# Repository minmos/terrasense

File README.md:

### Quick Overview
* **`firmware`**: contains the esp-idf firmware running on the esp32c6
* **`cad`**: contains the CAD files for the case housing the sockets, the 12V PSU, the relais/hv pcb, and an extension for that box housing the main pcb
* **`pcb`**: contains the KiCad files for the relais/hv pcb as well as the main pcb

### DEMO
Here is a quick demo video of our Terrasense implementation in action:

https://github.com/user-attachments/assets/7964f494-83c7-4bb1-9dd9-c3dd94d3becd

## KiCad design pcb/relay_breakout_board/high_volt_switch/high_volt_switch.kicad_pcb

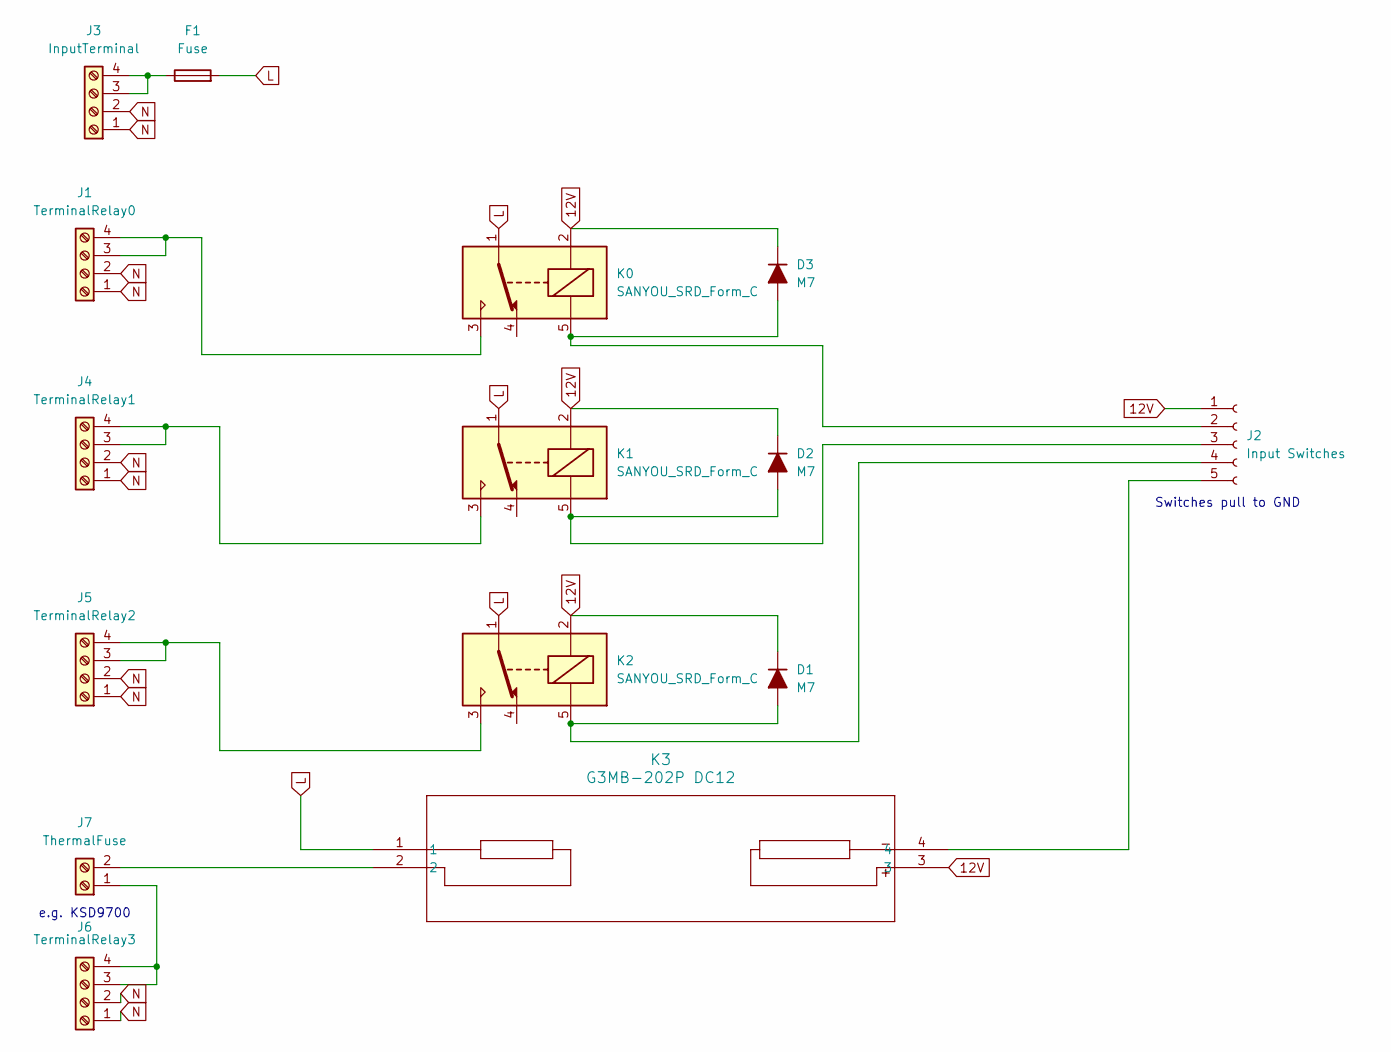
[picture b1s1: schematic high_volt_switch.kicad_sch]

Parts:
D1, D2, D3: M7; D_SMA
F1: Fuse; Fuseholder_Cylinder-5x20mm_Schurter_0031_8201_Horizontal_Op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
J1: TerminalRelay0; Altech_AK100_1x04_P5.00mm
J2: Input Switches; JST_XH_B5B-XH-A_1x05_P2.50mm_Vertical
J3: InputTerminal; Altech_AK100_1x04_P5.00mm
J4: TerminalRelay1; Altech_AK100_1x04_P5.00mm
J5: TerminalRelay2; Altech_AK100_1x04_P5.00mm
J6: TerminalRelay3; Altech_AK100_1x04_P5.00mm
J7: ThermalFuse; Altech_AK100_1x02_P5.00mm
K0, K1, K2: SANYOU_SRD_Form_C; Relay_SPDT_SANYOU_SRD_Series_Form_C
K3: G3MB-202P DC12; G3MB-202P DC5_OMR

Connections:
12V: D1.1 (K), D2.1 (K), D3.1 (K), J2.1, K0.2, K1.2, K2.2, K3.3
L: F1.2, K0.1, K1.1, K2.1, K3.1
N: J1.1, J1.2, J3.1, J3.2, J4.1, J4.2, J5.1, J5.2, J6.1, J6.2
unnamed: D1.2 (A), J2.4, K2.5
unnamed: D2.2 (A), J2.3, K1.5
unnamed: D3.2 (A), J2.2, K0.5
unnamed: J1.3, J1.4, K0.3
unnamed: J2.5, K3.4
unnamed: F1.1, J3.3, J3.4
unnamed: J4.3, J4.4, K1.3
unnamed: J5.3, J5.4, K2.3
unnamed: J6.3, J6.4, J7.1
unnamed: J7.2, K3.2

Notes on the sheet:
Switches pull to GND
e.g. KSD9700

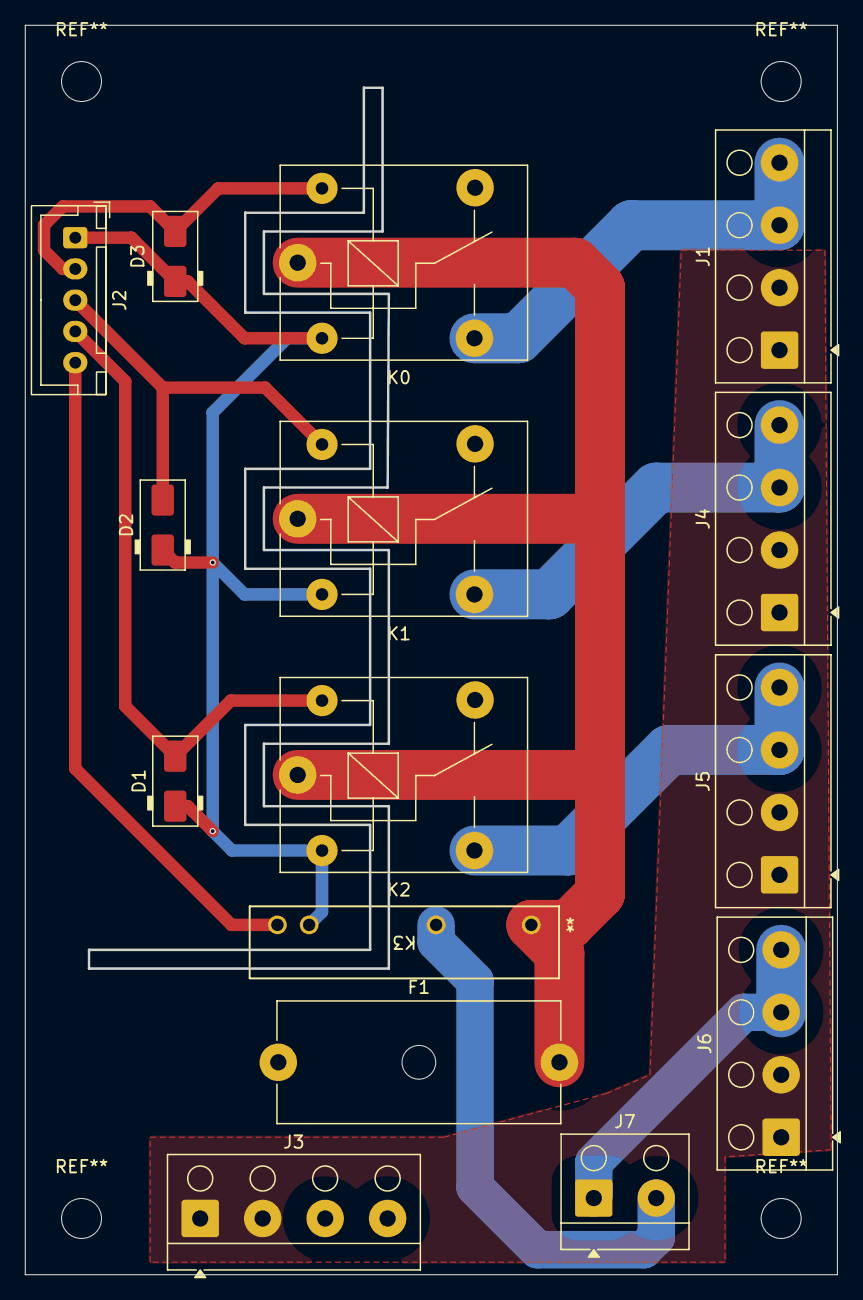
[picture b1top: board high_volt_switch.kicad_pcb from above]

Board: 2 copper layers, 64.9 x 99.9 mm, 15 parts (0 on the bottom side), 13 nets.

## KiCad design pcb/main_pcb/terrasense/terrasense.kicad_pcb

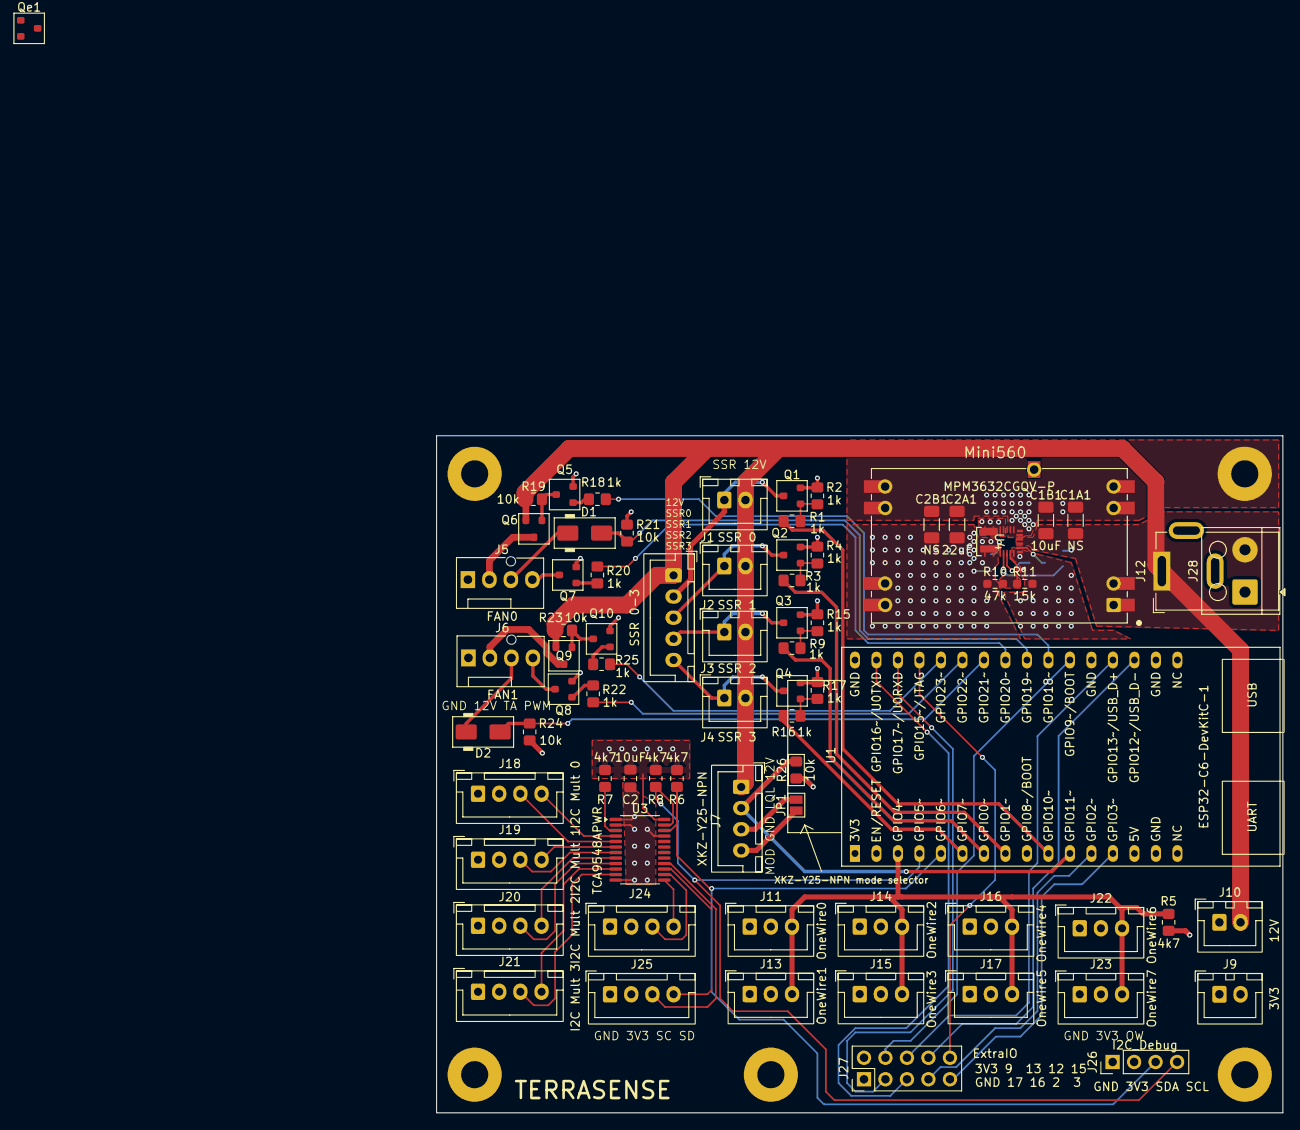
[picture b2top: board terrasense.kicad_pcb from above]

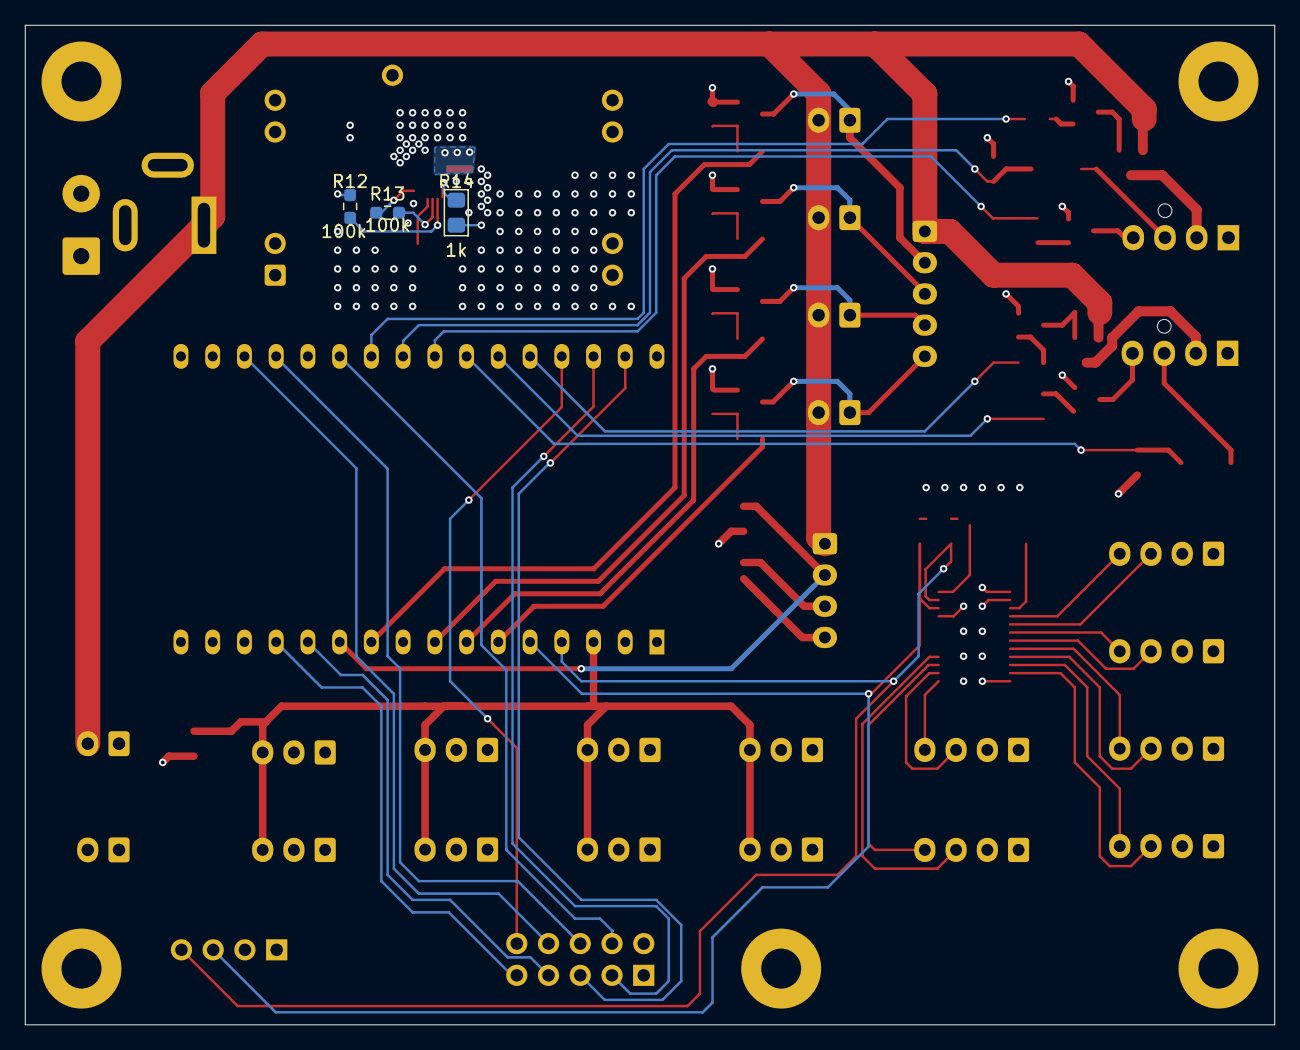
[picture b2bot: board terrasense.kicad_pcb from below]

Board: 4 copper layers, 100.0 x 80.0 mm, 77 parts (3 on the bottom side), 65 nets.

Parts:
C1A1, C2B1: NS; C_1206_3216Metric_Pad1.33x1.80mm_HandSolder
C1B1: 10uF; C_1206_3216Metric_Pad1.33x1.80mm_HandSolder
C2: 10uF; C_0805_2012Metric_Pad1.18x1.45mm_HandSolder
C2A1: 22uF; C_1206_3216Metric_Pad1.33x1.80mm_HandSolder
D1, D2: M7; D_SMA
J1: SSR 0; JST_XH_B2B-XH-A_1x02_P2.50mm_Vertical
J2: SSR 1; JST_XH_B2B-XH-A_1x02_P2.50mm_Vertical
J3: SSR 2; JST_XH_B2B-XH-A_1x02_P2.50mm_Vertical
J4: SSR 3; JST_XH_B2B-XH-A_1x02_P2.50mm_Vertical
J5: FAN0; FanPinHeader_1x04_P2.54mm_Vertical
J6: FAN1; FanPinHeader_1x04_P2.54mm_Vertical
J7: XKZ-Y25-NPN; JST_XH_B4B-XH-A_1x04_P2.50mm_Vertical
J8: SSR 0-3; JST_XH_B5B-XH-A_1x05_P2.50mm_Vertical
J9: 3V3; JST_XH_B2B-XH-A_1x02_P2.50mm_Vertical
J10: 12V; JST_XH_B2B-XH-A_1x02_P2.50mm_Vertical
J11: OneWire0; JST_XH_B3B-XH-A_1x03_P2.50mm_Vertical
J12: 12V In; BarrelJack_GCT_DCJ200-10-A_Horizontal
J13: OneWire1; JST_XH_B3B-XH-A_1x03_P2.50mm_Vertical
J14: OneWire2; JST_XH_B3B-XH-A_1x03_P2.50mm_Vertical
J15: OneWire3; JST_XH_B3B-XH-A_1x03_P2.50mm_Vertical
J16: OneWire4; JST_XH_B3B-XH-A_1x03_P2.50mm_Vertical
J17: OneWire5; JST_XH_B3B-XH-A_1x03_P2.50mm_Vertical
J18: I2C Mult 0; JST_XH_B4B-XH-A_1x04_P2.50mm_Vertical
J19: I2C Mult 1; JST_XH_B4B-XH-A_1x04_P2.50mm_Vertical
J20: I2C Mult 2; JST_XH_B4B-XH-A_1x04_P2.50mm_Vertical
J21: I2C Mult 3; JST_XH_B4B-XH-A_1x04_P2.50mm_Vertical
J22: OneWire6; JST_XH_B3B-XH-A_1x03_P2.50mm_Vertical
J23: OneWire7; JST_XH_B3B-XH-A_1x03_P2.50mm_Vertical
J24: I2C Mult 4; JST_XH_B4B-XH-A_1x04_P2.50mm_Vertical
J25: I2C Mult 5; JST_XH_B4B-XH-A_1x04_P2.50mm_Vertical
J26: I2C_Debug; PinHeader_1x04_P2.54mm_Vertical
J27: ExtraIO; PinHeader_2x05_P2.54mm_Vertical
J28: 12V_In; Altech_AK100_1x02_P5.00mm
JP1: XKZ-Y25-NPN mode selector; SolderJumper-2_P1.3mm_Open_Pad1.0x1.5mm
Q1, Q2, Q3, Q4, Q5, Q7, Q8, Q10: MMBT2222A; SOT-23
Q6, Q9: A3401; SOT-23
Qe1: A3401; SOT-23
R1, R2, R3, R4, R9, R14, R15, R16, R17, R18, R20, R22, R25: 1k; R_0805_2012Metric_Pad1.20x1.40mm_HandSolder
R5, R6, R7, R8: 4k7; R_0805_2012Metric_Pad1.20x1.40mm_HandSolder
R10: 47k; R_0603_1608Metric_Pad0.98x0.95mm_HandSolder
R11: 15k; R_0603_1608Metric_Pad0.98x0.95mm_HandSolder
R12, R13: 100k; R_0603_1608Metric_Pad0.98x0.95mm_HandSolder
R19, R21, R23, R24, R26: 10k; R_0805_2012Metric_Pad1.20x1.40mm_HandSolder
U1: ESP32-C6-DevKitC-1
U2: Mini560
U3: TCA9548APWR; TSSOP-24_4.4x7.8mm_P0.65mm
U4: MPM3632CGQV-P; QFN3p0x5p0x1p6_MPM3632C_MNP

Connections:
3V3: C2.1, C2A1.1, C2B1.1, J9.2, J11.2, J13.2, J14.2, J15.2, J16.2, J17.2, J18.2, J19.2, J20.2, J21.2, J22.2, J23.2, J24.2, J25.2, J26.2, J27.2, R5.2, R6.1, R7.1, R8.1, R10.1, R14.2, R21.1, R24.1, R26.1, U1.1 (3V3), U2.8 (VOUT+), U2.9 (VOUT+), U3.24 (VCC), U4.8 (OUT), U4.9 (OUT)
12V: C1A1.1, C1B1.1, J1.2, J2.2, J3.2, J4.2, J7.1, J8.1, J10.2, J12.1, J28.2, Q6.2 (S), Q9.2 (S), Qe1.2 (S), R12.1, R19.2, R23.2, U2.1 (VIN+), U2.2 (VIN+), U4.17 (VIN), U4.18 (VIN)
/FAN/FAN_0_12V_PWM: R18.2, U1.23 (GPIO18)
/FAN/FAN_0_PWM: R20.1, U1.25 (GPIO20)
/FAN/FAN_0_TACHO: D1.2 (A), R21.2, U1.24 (GPIO19)
/FAN/FAN_1_12V_PWM: R25.2, U1.28 (GPIO23)
/FAN/FAN_1_PWM: R22.1, U1.27 (GPIO22)
/FAN/FAN_1_TACHO: D2.2 (A), R24.2, U1.26 (GPIO21)
/GPIO2: J27.7, U1.12 (GPIO2)
/GPIO3: J27.9, U1.13 (GPIO3)
/GPIO9/BOOT: J27.4, U1.22 (GPIO9/BOOT)
/GPIO12/USB_D-: J27.8, U1.19 (GPIO12/USB_D-)
/GPIO13/USB_D+: J27.6, U1.20 (GPIO13/USB_D+)
/GPIO15/JTAG: J27.10, U1.29 (GPIO15/JTAG)
/GPIO16/U0TXD: J27.5, U1.31 (GPIO16/U0TXD)
/GPIO17/U0RXD: J27.3, U1.30 (GPIO17/U0RXD)
/I2C_MULT/I2C_SCL: J26.3, R6.2, U1.5 (GPIO6), U3.22 (SCL)
/I2C_MULT/I2C_SDA: J26.4, R8.2, U1.4 (GPIO5/MTDI), U3.23 (SDA)
/I2C_MULT/SC0: J18.3, U3.5 (SC0)
/I2C_MULT/SC1: J19.3, U3.7 (SC1)
/I2C_MULT/SC2: J20.3, U3.9 (SC2)
/I2C_MULT/SC3: J21.3, U3.11 (SC3)
/I2C_MULT/SC4: J24.3, U3.14 (SC4)
/I2C_MULT/SC5: J25.3, U3.16 (SC5)
/I2C_MULT/SD0: J18.4, U3.4 (SD0)
/I2C_MULT/SD1: J19.4, U3.6 (SD1)
/I2C_MULT/SD2: J20.4, U3.8 (SD2)
/I2C_MULT/SD3: J21.4, U3.10 (SD3)
/I2C_MULT/SD4: J24.4, U3.13 (SD4)
/I2C_MULT/SD5: J25.4, U3.15 (SD5)
/LIQUID_LEVEL/LIQUID_LEVEL: J7.2, R26.2, U1.11 (GPIO11)
/ONE_WIRE/OneWire: J11.3, J13.3, J14.3, J15.3, J16.3, J17.3, J22.3, J23.3, R5.1, U1.3 (GPIO4/MTMS)
/SSR/SSR_0_CTRL: R1.1, U1.10 (GPIO10)
/SSR/SSR_1_CTRL: R3.1, U1.8 (GPIO1)
/SSR/SSR_2_CTRL: R9.1, U1.7 (GPIO0)
/SSR/SSR_3_CTRL: R16.1, U1.6 (GPIO7)
/STEP_DOWN/EN: R12.2, U4.11 (EN)
/STEP_DOWN/VCC: R13.1, U4.16 (VCC)
GND: C1A1.2, C1B1.2, C2.2, C2A1.2, C2B1.2, J5.1, J6.1, J7.3, J9.1, J10.1, J11.1, J12.2, J13.1, J14.1, J15.1, J16.1, J17.1, J18.1, J19.1, J20.1, J21.1, J22.1, J23.1, J24.1, J25.1, J26.1, J27.1, J28.1, JP1.2 (B), Q1.2 (E), Q2.2 (E), Q3.2 (E), Q4.2 (E), Q5.2 (E), Q7.2 (E), Q8.2 (E), Q10.2 (E), R2.1, R4.1, R11.2, R15.1, R17.1, U1.15 (GND), U1.18 (GND), U1.21 (GND), U1.32 (GND), U2.3 (GND), U2.4 (GND), U2.6 (GND), U2.7 (GND), U3.1 (A0), U3.2 (A1), U3.12 (GND), U3.21 (A2), U4.1 (PGND), U4.2 (PGND), U4.14 (AGND), U4.15 (AGND), U4.19 (PGND), U4.20 (PGND)
unnamed: D1.1 (K), J5.3
unnamed: D2.1 (K), J6.3
unnamed: J1.1, J8.2, Q1.3 (C)
unnamed: J2.1, J8.3, Q2.3 (C)
unnamed: J3.1, J8.4, Q3.3 (C)
unnamed: J4.1, J8.5, Q4.3 (C)
unnamed: J5.2, Q6.3 (D)
unnamed: J5.4, Q7.3 (C)
unnamed: J6.2, Q9.3 (D), Qe1.3 (D)
unnamed: J6.4, Q8.3 (C)
unnamed: J7.4, JP1.1 (A)
unnamed: Q1.1 (B), R1.2, R2.2
unnamed: Q2.1 (B), R3.2, R4.2
unnamed: Q3.1 (B), R9.2, R15.2
unnamed: Q4.1 (B), R16.2, R17.2
unnamed: Q5.1 (B), R18.1
unnamed: Q5.3 (C), Q6.1 (G), R19.1
unnamed: Q7.1 (B), R20.2
unnamed: Q8.1 (B), R22.2
unnamed: Q10.1 (B), R25.1
unnamed: Q9.1 (G), Q10.3 (C), Qe1.1 (G), R23.1
unnamed: R7.2, U3.3 (~RESET)
unnamed: R10.2, R11.1, U4.13 (FB)
unnamed: R14.1, U4.10 (OUT_SENSE)
unnamed: R13.2, U4.12 (PG)
unnamed: U4.4 (SW), U4.5 (SW), U4.6 (SW), U4.7 (SW)

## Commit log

2026-04-27 init pcb v0.1
2026-04-29 first init of esp-idf firmware, wifi and mqtt are working already
2026-04-29 update default to use correct esp board
2026-04-29 added basic OTA functionality
2026-05-05 esp README info
2026-05-07 basic ds18b20 integration, including mutex protected sensor values polling in sensor.c
2026-05-07 OTA still works with increased flash storage
2026-05-07 cleanup using dedicated sys_config.h for hardware and pin configurations
2026-05-07 added ds18b20 address discovery ESP-IDF project
2026-05-11 minor cleanup + mqtt naming scheme proposal
2026-05-11 damn huge mqtt cleanup. logic split up into app_logic. Hass autodiscovery and sensor data publish handled by app_logic. OTA still works
2026-05-11 compile-time opt-in flag for DS18B20 sensor
2026-05-13 basic SHT35 example in app_logic.c
2026-05-13 single SHT35 supported, TODO: need I2C multiplexer support. HASS autodiscovery supports multiple entities through unique id
2026-05-18 Added I2C integration with TCA9548A MUX
2026-05-18 binary sensor integration
2026-05-19 basic gpio switch for SSR with subscribe example
2026-05-20 added debug led for sensor component
2026-05-20 slight builtin led cleanup
2026-05-20 granular debug support for some components
2026-05-27 new esp
2026-05-27 GRB and RGB switching
2026-05-27 Relais and SSR work
2026-05-27 fan integration for 3pin and 4pin fan, including RPM for 4pin fans. all with HA autodiscovery
2026-05-27 hass autodiscovery for number entity
2026-05-27 small config changes for 8mb esp32c6 and enabled https for ota
2026-05-27 added print for dns server
2026-05-27 added control task
2026-05-27 adapted sys_config.h
2026-05-27 update vscode config
2026-05-28 update test config; change mqtt subscibe location
2026-05-28 added control logic for crawl cay test setup
2026-06-01 clean README.md
2026-06-01 main.c cleanup
2026-06-01 sys_utils cleanup
2026-06-01 sys_ota cleanup
2026-06-01 sensor component cleanup
2026-06-01 net_mqtt component cleanup
2026-06-01 net_core component cleanup
2026-06-01 app_logic cleanup
2026-06-01 actors component cleanup
2026-06-02 limited decimal places to 1 for sht and ds18b20
2026-06-02 added support for multi terrarium config with menuconfig
2026-06-02 renamed a folder
2026-06-02 update pcb with ordered pcb
2026-06-02 renamed firmware project
2026-06-02 improved safety guards for crawl cay terrarium
2026-06-02 added system error sensor to autodiscovery for text based error messages and fixed a typo for setup detection
2026-06-02 some small text changes
2026-06-03 small fixes in app_logic
2026-06-04 made uique id terrarium specific; added a small delay during auto discovery to ensure everything is received by the broker
2026-06-04 update dockerfile for podman
2026-06-05 added cad files for a colleague
2026-06-07 added readme with the video
2026-06-07 is the video now nicely embedded?
